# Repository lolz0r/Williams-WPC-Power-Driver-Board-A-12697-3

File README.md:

# Williams WPC power/driver replacement

> **WARNING: These are unverified, experimental boards. Use at your own risk.**
> No variant has been physically validated or qualified for production. Simulation
> results, CAD checks and manufacturing files do not establish safe or reliable
> operation. Errors may damage the board, connected equipment or pinball machine.
> Independently review the design and complete first-article testing before use.

This project develops a modern replacement for the Williams **A-12697-3 WPC
Power/Driver Board**, with **Star Trek: The Next Generation L7** as the documented
compatibility and emulation target. It provides rectified supplies, regulated
5 V and 12 V rails, 28 coil/flasher outputs, an 8×8 lamp matrix and five general
illumination triac channels. The board has no firmware. Compatibility with every
A-12697 installation has not been established.

## Variants and sourcing options

| Location | What it contains | Quantity and status |
| --- | --- | --- |
| [JLC-100](variants/jlcpcb-100/README.md) | Latest separate native KiCad variant, derived from JLC-3 with stocked alternative parts, mixed SMT/through-hole assembly files and connector-orientation guides. | Electronics selected for **100 boards plus spares**, using dated JLCPCB inventory snapshots. Experimental; software checks pass, physical and assembler acceptance gates remain open. |
| [JLC-3](variants/jlcpcb/README.md) | Earlier JLCPCB prototype with TPS552892 buck-boost supplies. Its CAD and exports are independent of JLC-100. | Prototype revision with procurement shortfalls. Its standard upload pair covers SMT; through-hole/manual parts and hardware use separate lists. |
| [DigiKey one-board sourcing proposal](variants/jlcpcb-100/output/digikey-1/README.md) | Alternative procurement BOM and itemized USD pricing based on the JLC-100 design. **This is not another released PCB or CPL.** | **One board, no production spares.** Some parts are proposed substitutes requiring engineering review; F115 remains unresolved and unpriced. |
| [Original cost-reduced project](docs/RELEASE_STATUS.md) at the repository root | Preserved parent CAD, earlier regulator design, simulation work and release-candidate exports. | Earlier engineering candidate with its own unresolved verification gates. Root `output/` does not contain the JLC-100 variant. |

Choose the variant first, then use its matching CAD, Gerbers, BOM and CPL.
Substitutions, packages and placement rotations differ between variants.
JLC-1/JLC-2 archives under `variants/jlcpcb/output/` are historical snapshots.

## JLC-100: Gerbers, BOM and centroids

For the latest JLCPCB variant, start with these files:

| File | Purpose |
| --- | --- |
| [Gerbers and drills ZIP](variants/jlcpcb-100/output/release-candidate/gerbers-and-drills.zip) | Bare-board fabrication layers and plated/non-plated drills. |
| [Combined electronics BOM.csv](variants/jlcpcb-100/output/release-candidate/jlcpcb-assembly/BOM.csv) | JLCPCB upload BOM covering all SMT and through-hole electronics, holders and fuse cartridges. |
| [Matching CPL.csv](variants/jlcpcb-100/output/release-candidate/jlcpcb-assembly/CPL.csv) | Matching component centers and corrected supplier placement rotations. Use with the combined BOM above. |
| [BOM/CPL bundle ZIP](variants/jlcpcb-100/output/wpc-JLC-100-BOM-CPL.zip) | Combined upload pair with assembly reference material. |
| [Complete prototype package ZIP](variants/jlcpcb-100/output/wpc-sttng-JLC-100-prototype.zip) | Native CAD, fabrication and assembly outputs, sourcing and recorded verification evidence. |
| [Complete components BOM](variants/jlcpcb-100/output/release-candidate/bom/all-components.csv) | Human-readable assembly/procurement record, including external hardware and zero-quantity DNP/board features. |
| [100-board electronics purchase BOM](variants/jlcpcb-100/output/release-candidate/bom/jlc-electronics-purchase.csv) | Order quantities and stock evidence, including procurement spares. This is not the upload BOM. |
| [External hardware BOM](variants/jlcpcb-100/output/release-candidate/bom/external-hardware.csv) | Heatsinks, screws, nuts and thermal paste for separate procurement and manual fitting. |
| [Native KiCad PCB](variants/jlcpcb-100/wpc_power_driver_cost.kicad_pcb), [schematic](variants/jlcpcb-100/wpc_power_driver_cost.kicad_sch) and [assembly preview](variants/jlcpcb-100/output/release-candidate/3d/perspective.png) | Source design and nominal assembled geometry. |

The combined upload pair describes **one board**. Select the production quantity
in the assembly order; do not multiply CPL entries or include purchasing spares
as placements. There are **440 electronic pieces per board: 345 SMT, 82 soldered
through-hole pieces and 13 inserted fuse cartridges**, grouped into 69 catalog
parts. J115 is purchased as two six-position headers. Separate fuse holders and
cartridges account for the other expanded references.

Read the [upload and manual-assembly instructions](variants/jlcpcb-100/docs/JLCPCB_UPLOAD.md)
and provide the [PCBA remarks](variants/jlcpcb-100/output/release-candidate/jlcpcb-assembly/PCBA-remark.txt).
The cartridge CPL entries use a documented 0.3 mm selection offset for stacked
parts; their physical centers remain at the holders. Heatsinks, fasteners and
paste are in the complete BOM but require separate sourcing and assembly
agreement. An accepted electronics upload alone does not establish complete
mechanical assembly.

Use the [connector orientation guide](variants/jlcpcb-100/output/release-candidate/jlcpcb-assembly/connector-orientation-guide.pdf)
and [preview review notes](variants/jlcpcb-100/docs/CONNECTOR_PREVIEW_REVIEW.md)
to resolve supplier-library discrepancies. The current CPL includes U1 = 90°,
U2/U3 = 270°, J110 = 180° and J113 = 90°; do not apply those offsets again.
J120/J121/J126 are present as C592598 / TE 1-640445-3 and need explicit part
selection and the documented header preparation. Several connector and rectifier
orientations still require assembler review.

For SMT-only work, use the separate [SMT BOM](variants/jlcpcb-100/output/release-candidate/bom/jlc-smt-bom.csv)
and [SMT CPL](variants/jlcpcb-100/output/release-candidate/assembly/jlc-smt-cpl.csv),
with the [through-hole/manual BOM](variants/jlcpcb-100/output/release-candidate/bom/jlc-through-hole-manual.csv)
for the remaining electronics. Generic engineering position reports are not the
assembly upload pair.

The JLC-100 fabrication specification is **four layers, 1.6 mm nominal FR-4,
2 oz finished outer copper / 1 oz inner copper** (70/35/35/70 µm), ENIG and at
least 20 µm finished plated-hole barrel copper. The outline is
449.152 × 272.910 mm. See [FABRICATION.txt](variants/jlcpcb-100/output/release-candidate/FABRICATION.txt)
and [READINESS.json](variants/jlcpcb-100/output/release-candidate/READINESS.json)
for the exact requirements and outstanding gates.

## DigiKey: one-board BOM and pricing

- [DigiKey BOM.csv](variants/jlcpcb-100/output/digikey-1/DigiKey-BOM.csv): original
  and proposed parts, order numbers, references, required/purchase quantities,
  through-hole parts, hardware and substitution notes.
- [Itemized pricing.csv](variants/jlcpcb-100/output/digikey-1/DigiKey-pricing.csv):
  per-part USD prices, quantity breaks, stock snapshots, product source links,
  extended costs and subtotal/complete-total rows.
- [Totals.csv](variants/jlcpcb-100/output/digikey-1/DigiKey-totals.csv): category
  subtotals, minimum-purchase overhead and missing-cost status.
- [DigiKey package ZIP](variants/jlcpcb-100/output/DigiKey-one-board.zip) and
  [sourcing explanation](variants/jlcpcb-100/output/digikey-1/README.md).

The September 14, 2026 estimate has a **$405.60 USD priced purchase subtotal**,
including minimum hardware purchase quantities. Parts allocated to one board
account for $363.30, including one complete thermal-paste syringe; $42.30 is
minimum-purchase excess. Freight, taxes, tariffs, PCB fabrication and assembly
are additional.

**This is a partial estimate: 78 of 79 required procurement lines are priced.**
F115's 0.75 A ceramic time-delay fuse remains required and unpriced, so the final
complete-BOM total is blank. The 28 priced candidate/accessory lines require
engineering review; the JLC-100 SPICE results do not qualify these substitutions.
No DigiKey-specific PCB, Gerbers or CPL has been released.

## Verification and reproduction

JLC-100 retains 230 passing ngspice engineering cases and recorded CAD,
manufacturing, inventory and assembly-file checks. These use engineering models,
including an averaged supply controller. They do not establish physical thermal,
fault, startup, harness-fit or production performance. Stock snapshots are not
reservations. Supplier part selection and manual operations remain review items.

See the variant's [simulation scope](variants/jlcpcb-100/docs/SPICE_SCOPE.md),
[inventory and assembly notes](variants/jlcpcb-100/docs/INVENTORY_AND_ASSEMBLY.md),
[first-article procedure](variants/jlcpcb-100/docs/FIRST_ARTICLE.md), and
[accepted verification manifest](variants/jlcpcb-100/output/release-candidate/reports/verification-manifest.json).
The later [native connector-tab audit](variants/jlcpcb-100/output/verification/revision/native-connector-tabs.json)
checks 37 single-row connector wall directions in nominal CAD; J113 and physical
cable compatibility retain the documented limitations. That audit and the
DigiKey proposal are additional repository records outside the existing complete
prototype ZIP.

Each variant's routed native PCB is authoritative. Open it with its adjacent
schematics, local symbols, footprints and models. Historical placement generators
and one-time migrations must not overwrite the routed source. Follow the chosen
variant's README and verification instructions when regenerating exports.

The large catalog-search cache is retained as lossless gzip; see the
[research storage notes](variants/jlcpcb-100/research/README.md) to unpack it.

The DigiKey CSVs can be regenerated from their saved pricing facts at the
repository root:

```sh
python3 variants/jlcpcb-100/tools/build_digikey_one_board.py
```

For the preserved parent project, use its [release status](docs/RELEASE_STATUS.md),
[verification instructions](docs/VERIFICATION.md), [Gerbers](output/release-candidate/gerbers-and-drills.zip),
[purchase BOM](output/release-candidate/bom/purchase-bom.csv),
[schematic PDF](output/release-candidate/schematic/schematic.pdf) and
[fabrication specification](output/release-candidate/FABRICATION.txt).
Older root exports directly under `output/` are superseded by the parent's
`output/release-candidate/`. The [historical design narrative](docs/HISTORICAL_DESIGN.md)
records earlier selections and estimates.

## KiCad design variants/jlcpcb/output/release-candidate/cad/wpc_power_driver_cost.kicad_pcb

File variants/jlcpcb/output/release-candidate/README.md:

# JLC-3 controlled prototype

Upload the matching `gerbers-and-drills.zip`, `bom/jlc-smt-bom.csv` and
`assembly/jlc-smt-cpl.csv` to JLCPCB. See `READINESS.json` and
`docs/PROTOTYPE_JLC3.md` for build scope, settings and first-article checks.
Through-hole/manual parts and hardware are listed separately in `bom/`.
Editable KiCad 10 sources, libraries and models are in `cad/`.
This package supports building a test prototype; physical qualification remains to be performed.

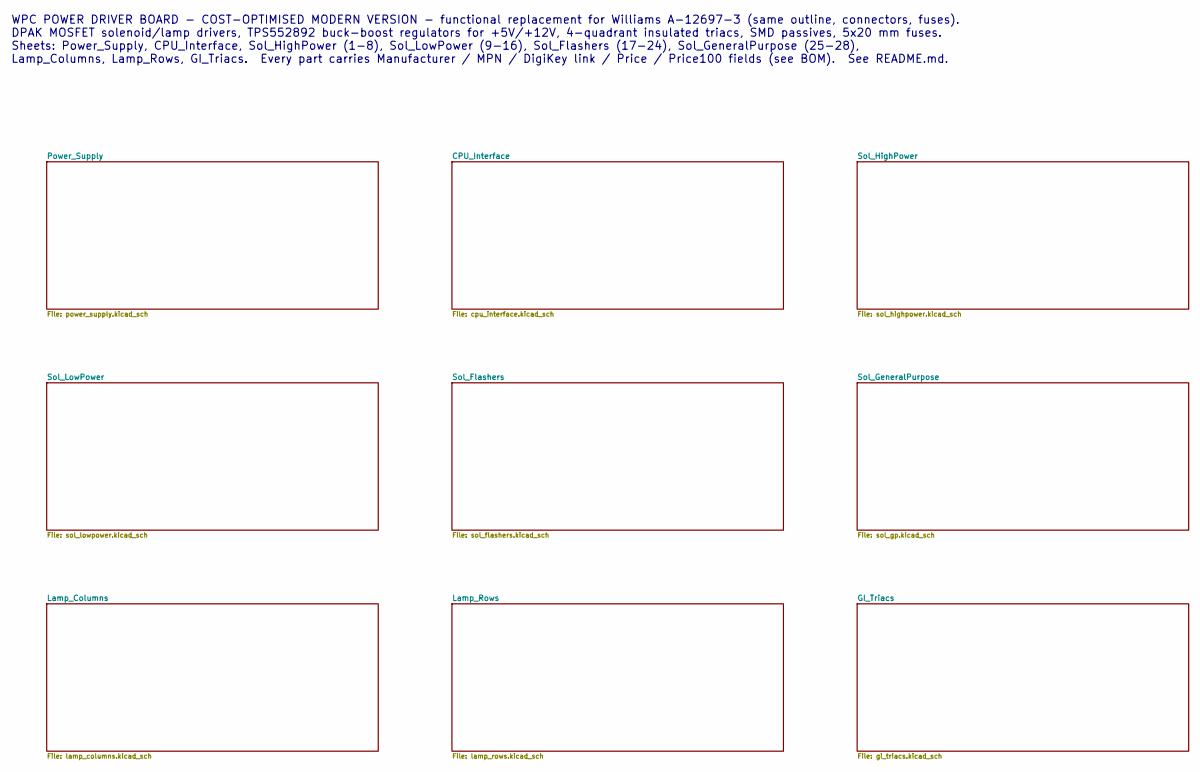
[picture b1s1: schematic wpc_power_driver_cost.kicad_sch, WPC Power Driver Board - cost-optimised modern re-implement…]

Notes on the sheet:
WPC POWER DRIVER BOARD - COST-OPTIMISED MODERN VERSION - functional replacement for Williams A-12697-3 (same outline, connectors, fuses). DPAK MOSFET solenoid/lamp drivers, TPS552892 buck-boost regulators for +5V/+12V, 4-quadrant insulated triacs, SMD passives, 5x20 mm fuses. Sheets: Power_Supply, 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

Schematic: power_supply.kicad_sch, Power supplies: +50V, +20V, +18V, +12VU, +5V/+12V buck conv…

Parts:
BR3: GBPC3510; Diode_Bridge_28.6x28.6x7.3mm_P18.0mm_P11.6mm; MPN GBPC3510W-E4/51; JLCPCB Part C435891
C2, C4, C9, C12: 330uF; CP_Radial_D8.0mm_P5.00mm; MPN EEU-FR1E331B; JLCPCB Part C1579638
C5, C6, C7, C11, C30: 10000uF 35V; CP_Radial_D26.0mm_P10.00mm_SnapIn; MPN B41252A7109M000; JLCPCB Part C6130373
C8, C32: 2200uF 100V; CP_Radial_D25.0mm_P10.00mm_SnapIn; MPN LLS2A222MELA; JLCPCB Part C1582025
C33, C34, C38, C39, C40, C44, C46, C49, C50, C51, C53, C56, C57, C58: 10uF; C_1210_3225Metric; MPN CL32B106KBJNNWE; JLCPCB Part C3844168
C35, C41, C45, C47, C48, C52, C54, C55: 100nF; C_0402_1005Metric; MPN GRM155R71H104KE14D; JLCPCB Part C77020
C36: 100nF; C_0805_2012Metric; MPN CC0805KRX7R9BB104; JLCPCB Part C49678
C37: 680pF; C_0805_2012Metric; MPN CC0805JRNPO9BN681; JLCPCB Part C107121
C42: 330nF; C_0805_2012Metric; MPN CL21B334KBFNNNE; JLCPCB Part C73142
C43: 1nF; C_0805_2012Metric; MPN CC0805JRNPO9BN102; JLCPCB Part C62774
D101, D102, D103, D104: STPS20M100ST; TO220_Schottky_AKA_5772; MPN STPS20M100ST; JLCPCB Part C222114
D105, D106, D107, D108, D109, D110, D111, D112, D113, D114, D115, D116: STPS20M100S; D2PAK_Schottky_AKA; MPN STPS20M100SG-TR; JLCPCB Part C969989
F103, F104, F105, F116: 3A S.B.; Fuseholder_Clip-5x20mm_Keystone_3517_Inline_P23.11x6.76mm_D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; MPN 0239003.MXP; JLCPCB Part C142824
F111, F113: 5A S.B.; Fuseholder_Clip-5x20mm_Keystone_3517_Inline_P23.11x6.76mm_D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; MPN 0239005.MXP; JLCPCB Part C151086
F112: 7A S.B.; Fuseholder_Clip-5x20mm_Keystone_3517_Inline_P23.11x6.76mm_D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; MPN 0239007.MXP; JLCPCB Part C3161084
F114: 8A; Fuseholder_Clip-5x20mm_Keystone_3517_Inline_P23.11x6.76mm_D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; MPN 0217008.MXP; JLCPCB Part C2936126
F115: 3/4A S.B.; Fuseholder_Clip-5x20mm_Keystone_3517_Inline_P23.11x6.76mm_D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; MPN 0239.750MXP; JLCPCB Part C3157012
H1, H2, H3, H4, H5, H6, H7, H8: M4; MountingHole_4.3mm_M4
J101: J101 xformer 9VAC (Red) / 13VAC (Blu-Wht); Molex_KK-396_A-41791-0007_1x07_P3.96mm_Vertical; MPN 26604070; JLCPCB Part C587091
J102: J102 xformer 16VAC (Wht-Red) / solenoid ~51VAC (B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; Molex_KK-396_A-41791-0009_1x09_P3.96mm_Vertical; MPN 0026604090; JLCPCB Part C17420444
J103: J103 ground to 8-driver board (all four pins grou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; Molex_KK-396_A-41791-0004_1x04_P3.96mm_Vertical; MPN 26604040; JLCPCB Part C240824
J104: J104 fused 51VAC (F112, pins 1/2) to Fliptronic I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; Molex_KK-396_A-41791-0005_1x05_P3.96mm_Vertical; MPN 26604050; JLCPCB Part C505166
J106: J106 +20V to backbox flashlamps (pins 1-4 open, k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; Molex_KK-396_A-41791-0005_1x05_P3.96mm_Vertical; MPN 26604050; JLCPCB Part C505166
J107: J107 +50V (F103/F104/F105) and +20V (pins 5,6) to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; Molex_KK-396_A-41791-0006_1x06_P3.96mm_Vertical; MPN 0026604060; JLCPCB Part C17656945
J108: J108 +50V (F103/F104/F105) to cabinet (N/C on STT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; Molex_KK-396_A-41791-0003_1x03_P3.96mm_Vertical; MPN 26604030; JLCPCB Part C240823
J109: J109 spare (N/C); Molex_KK-396_A-41791-0007_1x07_P3.96mm_Vertical; MPN 26604070; JLCPCB Part C587091
J110: J110 spare (N/C); Molex_KK-396_A-41791-0009_1x09_P3.96mm_Vertical; MPN 0026604090; JLCPCB Part C17420444
J112: J112 xformer 9.8VAC (Wht-Grn); Molex_KK-396_A-41791-0005_1x05_P3.96mm_Vertical; MPN 26604050; JLCPCB Part C505166
J114: J114 +12V/+5V/GND to CPU J210, Fliptronic J904, 8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; Molex_KK-396_A-41791-0007_1x07_P3.96mm_Vertical; MPN 26604070; JLCPCB Part C587091
J116: J116 +12V power (unregulated) / GND / +5V to coin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; Molex_KK-396_A-41791-0004_1x04_P3.96mm_Vertical; MPN 26604040; JLCPCB Part C240824
J117: J117 +12V power (unregulated) / GND / +5V to DMD 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; Molex_KK-396_A-41791-0004_1x04_P3.96mm_Vertical; MPN 26604040; JLCPCB Part C240824
J118: J118 +12V power (unregulated) / GND / +5V to play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; Molex_KK-396_A-41791-0004_1x04_P3.96mm_Vertical; MPN 26604040; JLCPCB Part C240824
L1, L2: 10uH; L_Bourns_SRP1245A; MPN SRP1265A-100M; JLCPCB Part C840531
LED1, LED2, LED4, LED5, LED6, LED7: LED red; LED_0805_2012Metric; MPN NCD0805R1; JLCPCB Part C84256
R192: 470; R_0805_2012Metric; MPN 0805W8F4700T5E; JLCPCB Part C17710
R193: 1K; R_0805_2012Metric; MPN 0805W8F1001T5E; JLCPCB Part C17513
R194, R196, R250, R251: 1.5K; R_0805_2012Metric; MPN 0805W8F1501T5E; JLCPCB Part C4310
R259, R260: 15K; R_2512_6332Metric; MPN RC2512JK-0715KL; JLCPCB Part C1882622
R261: 118K; R_0805_2012Metric; MPN RC0805FR-07118KL; JLCPCB Part C274001
R262: 29.4K; R_0805_2012Metric; MPN RC0805FR-0729K4L; JLCPCB Part C273956
R263, R269: 49.9K; R_0805_2012Metric; MPN 0805W8F4992T5E; JLCPCB Part C17719
R264: 6.65K; R_0805_2012Metric; MPN RT0805BRD076K65L; JLCPCB Part C865625
R265: 2.1K; R_0805_2012Metric; MPN RT0805BRD072K1L; JLCPCB Part C865367
R266: 33.2K; R_0805_2012Metric; MPN 0805W8F3322T5E; JLCPCB Part C37252
R267: 130K; R_0805_2012Metric; MPN RC0805FR-07130KL; JLCPCB Part C483008
R268: 20K; R_0805_2012Metric; MPN 0805W8F2002T5E; JLCPCB Part C4328
R270: 18K; R_0805_2012Metric; MPN RT0805BRD0718KL; JLCPCB Part C706223
R271: 2K; R_0805_2012Metric; MPN RT0805BRD072KL; JLCPCB Part C865384
R272: 42.2K; R_0805_2012Metric; MPN 0805W8F4222T5E; JLCPCB Part C17686
R326: 13m; R_2512_6332Metric; MPN RL2512FK-070R013L; JLCPCB Part C705606
R327: 33m; R_2512_6332Metric; MPN RL2512FK-070R033L; JLCPCB Part C705608
TP1: TP1 +12VU; TestPoint_THTPad_D2.0mm_Drill1.0mm
TP2: TP2 +5V; TestPoint_THTPad_D2.0mm_Drill1.0mm
TP3: TP3 +12V; TestPoint_THTPad_D2.0mm_Drill1.0mm
TP5: TP5 GND; TestPoint_THTPad_D2.0mm_Drill1.0mm
TP6: TP6 +50V; TestPoint_THTPad_D2.0mm_Drill1.0mm
TP7: TP7 +20V; TestPoint_THTPad_D2.0mm_Drill1.0mm
TP8: TP8 +18V; TestPoint_THTPad_D2.0mm_Drill1.0mm
TP9: TP9 +5V_RAW; TestPoint_THTPad_D2.0mm_Drill1.0mm
U20, U21: TPS552892RYQR; TI_RYQ0021B_5x3mm; MPN TPS552892RYQR; JLCPCB Part C19272254

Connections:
+5V: C4.1, C9.1, J114.3, J114.4, J116.4, J117.4, J118.4, R192.1, R264.1, R326.2, TP2.1, U20.13 (ISN); also elsewhere on the board
+12V: C2.1, C12.1, F115.1, R193.1, R270.1, R327.2, TP3.1, U21.13 (ISN); also elsewhere on the board
+12VU: C30.1, D113.1 (K), D114.1 (K), J116.2, J117.2, J118.2, R250.1, TP1.1
+12V_F: F115.2, J114.1, J114.2, R251.1
+18V: C6.1, C7.1, C39.1, C40.1, C54.1, C56.1, C57.1, D101.1 (K), D102.1 (K), R196.1, R267.1, TP8.1, U21.7 (VIN); also elsewhere on the board
+20V: C11.1, D109.1 (K), D110.1 (K), J106.5, J107.5, J107.6, R194.1, TP7.1; also elsewhere on the board
+50V: BR3.1 (+), C8.1, C32.1, F103.1, F104.1, F105.1, R259.1, R260.1, TP6.1; also elsewhere on the board
+50V_F103: F103.2, J107.1, J108.1
+50V_F104: F104.2, J107.2, J108.2
+50V_F105: F105.2, J107.3, J108.3
/Power_Supply/+5V_RAW: C5.1, C33.1, C34.1, C47.1, C49.1, C50.1, D105.1 (K), D106.1 (K), R261.1, TP9.1, U20.7 (VIN)
/Power_Supply/AC13_A_F: D101.2 (A), D103.1 (K), F114.2
/Power_Supply/AC98_A_F: D113.2 (A), D115.1 (K), F116.2
/Power_Supply/U20_BOOT1: C35.1, U20.20 (BOOT1)
/Power_Supply/U20_BOOT2: C45.1, U20.19 (BOOT2)
/Power_Supply/U20_CC: C36.1, R266.2
/Power_Supply/U20_COMP: C37.1, R266.1, U20.15 (COMP)
/Power_Supply/U20_EN: R261.2, R262.1, U20.1 (EN)
/Power_Supply/U20_FB: R264.2, R265.1, U20.14 (FB)
/Power_Supply/U20_REG: C38.1, C48.1, C51.1, R326.1, U20.11 (VOUT), U20.12 (ISP)
/Power_Supply/U20_RT: R263.1, U20.6 (FSW)
/Power_Supply/U20_SW1: C35.2, L1.1, U20.8 (SW1)
/Power_Supply/U20_SW2: C45.2, L1.2, U20.10 (SW2)
/Power_Supply/U20_VCC: C46.1, U20.18 (VCC)
/Power_Supply/U21_BOOT1: C41.1, U21.20 (BOOT1)
/Power_Supply/U21_BOOT2: C52.1, U21.19 (BOOT2)
/Power_Supply/U21_CC: C42.1, R272.2
/Power_Supply/U21_COMP: C43.1, R272.1, U21.15 (COMP)
/Power_Supply/U21_EN: R267.2, R268.1, U21.1 (EN)
/Power_Supply/U21_FB: R270.2, R271.1, U21.14 (FB)
/Power_Supply/U21_REG: C44.1, C55.1, C58.1, R327.1, U21.11 (VOUT), U21.12 (ISP)
/Power_Supply/U21_RT: R269.1, U21.6 (FSW)
/Power_Supply/U21_SW1: C41.2, L2.1, U21.8 (SW1)
/Power_Supply/U21_SW2: C52.2, L2.2, U21.10 (SW2)
/Power_Supply/U21_VCC: C53.1, U21.18 (VCC)
AC9_A: F113.1, J101.1
AC9_AF: D105.2 (A), D107.1 (K), F113.2; also elsewhere on the board
AC9_B: D106.2 (A), D108.1 (K), J101.2; also elsewhere on the board
AC13_A: F114.1, J101.4, J101.5
AC13_B: D102.2 (A), D104.1 (K), J101.6, J101.7
AC16_A: F111.1, J102.1, J102.2
AC16_A_F: D109.2 (A), D111.1 (K), F111.2, J104.4; also elsewhere on the board
AC16_B: D110.2 (A), D112.1 (K), J102.3, J102.4, J104.5; also elsewhere on the board
AC98_A: F116.1, J112.1, J112.2
AC98_B: D114.2 (A), D116.1 (K), J112.3, J112.5
ACSOL_A: F112.1, J102.5, J102.6; also elsewhere on the board
ACSOL_A_F: BR3.3, F112.2, J104.1; also elsewhere on the board
ACSOL_B: BR3.4, J102.8, J102.9, J104.2; also elsewhere on the board

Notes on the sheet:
+50V solenoid supply (51 VAC winding -> ~70 V DC, 78 V peak unloaded)
BR4: discrete Schottky bridge D109-D112 (D2PAK tabs = cathodes: D109/D110 on the +20V pour, D111/D112 on the AC pours)
+20V flashlamp supply
BR1: D101-D104 STPS20M100ST TO-220, each with 577202B00000G heatsink (tabs/heatsinks = cathodes; do not join heatsinks)
+18V lamp matrix supply (13.3 VAC); also feeds the +12V digital buck-boost U21
BR2: discrete Schottky bridge D105-D108 (D2PAK tabs = cathodes: D105/D106 on the +5V_RAW pour, D107/D108 on the AC pours)
+5V raw supply (9VAC)
BR5: discrete Schottky bridge D113-D116 (D2PAK tabs = cathodes: D113/D114 on the +12VU pour, D115/D116 on the AC pours)
+12V POWER (unregulated, 9.8VAC): motors, optos, coin door, DMD - J116/J117/J118
Power supplies (windings per manual/pinwiki: 9 VAC red -> +5V, 13.3 VAC blu-wht -> +18V, 16 VAC wht-red -> +20V, 51 VAC blk-yel -> "+50V" (~70 V DC), 9.8 VAC wht-grn -> +12V power). Each secondary is fused (F111-F114, F116, 5x20 mm) before its bridge: GBPC3510W block (BR3, 6223BG basket heatsink); 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
U20: TPS552892 buck-boost / 395 kHz / PFM / +5V / current limit 3.85 A nominal
Local output ceramics precede the sense resistor; bulk capacitors and feedback follow it. EXTVCC open selects internal VCC.
U21: TPS552892 buck-boost / 395 kHz / PFM / +12V / current limit 1.52 A nominal

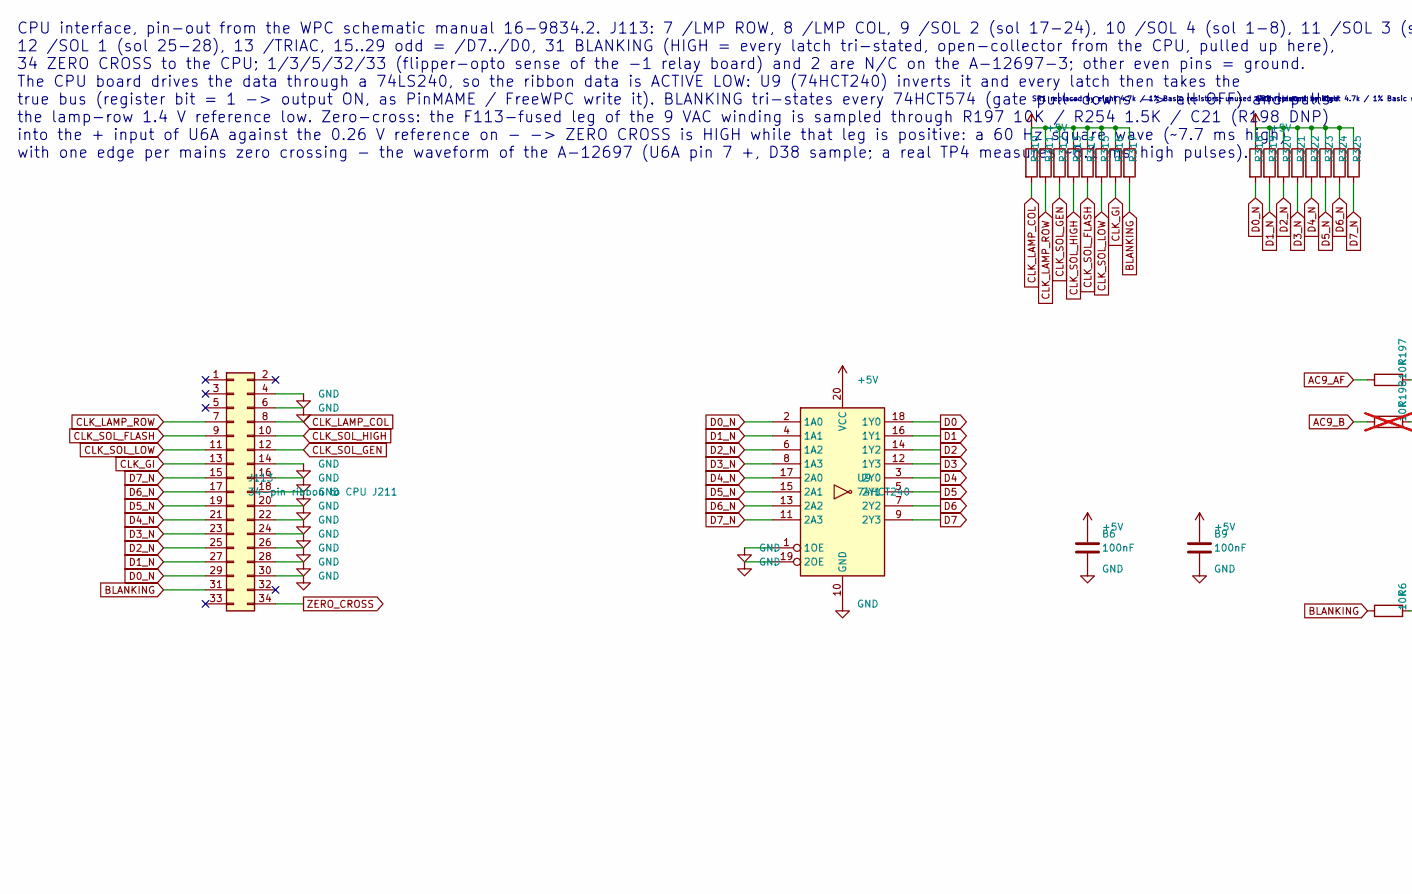
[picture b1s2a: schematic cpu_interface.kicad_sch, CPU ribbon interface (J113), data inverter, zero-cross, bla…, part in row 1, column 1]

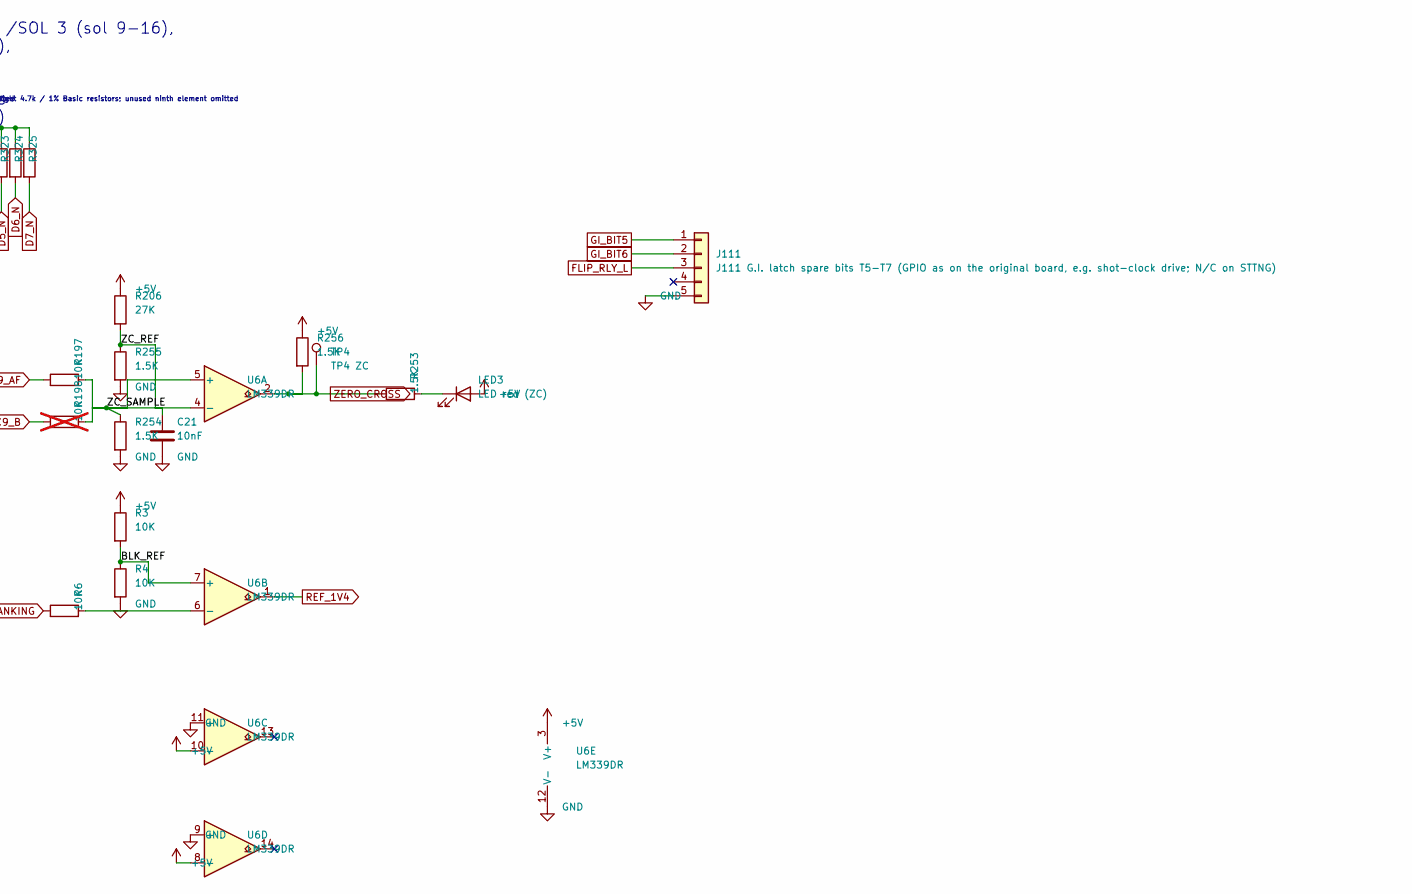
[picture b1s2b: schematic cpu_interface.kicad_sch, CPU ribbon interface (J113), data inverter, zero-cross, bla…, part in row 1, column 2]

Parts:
B6, B9: 100nF; C_0805_2012Metric; MPN CC0805KRX7R9BB104; JLCPCB Part C49678
C21: 10nF; C_0805_2012Metric; MPN CL21B103KBANNNC; JLCPCB Part C1710
J111: J111 G.I. latch spare bits T5-T7 (GPIO as on the 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; Molex_KK-254_AE-6410-05A_1x05_P2.54mm_Vertical; MPN 22232051; JLCPCB Part C588986
J113: 34-pin ribbon to CPU J211; 3M_N2534_6002_RB; MPN N2534-6002-RB; JLCPCB Part C17502444
LED3: LED red (ZC); LED_0805_2012Metric; MPN NCD0805R1; JLCPCB Part C84256
R3, R4, R6, R197: 10K; R_0805_2012Metric; MPN 0805W8F1002T5E; JLCPCB Part C17414
R198: 10K; R_0805_2012Metric; MPN RC0805FR-0710KL; not fitted
R206: 27K; R_0805_2012Metric; MPN 0805W8F2702T5E; JLCPCB Part C17593
R253, R254, R255, R256: 1.5K; R_0805_2012Metric; MPN 0805W8F1501T5E; JLCPCB Part C4310
R310, R311, R312, R313, R314, R315, R316, R317, R318, R319, R320, R321, R322, R323, R324, R325: 4.7K; R_0805_2012Metric; MPN 0805W8F4701T5E; JLCPCB Part C17673
TP4: TP4 ZC; TestPoint_THTPad_D2.0mm_Drill1.0mm
U6: LM339DR; SOIC-14_3.9x8.7mm_P1.27mm; MPN LM339DR; JLCPCB Part C7948
U9: 74HCT240; SOIC-20W_7.5x12.8mm_P1.27mm; MPN SN74HCT240DWR; JLCPCB Part C132264

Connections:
+5V: B6.1, B9.1, LED3.2 (A), R3.1, R206.1, R256.1, R310.1, R311.1, R312.1, R313.1, R314.1, R315.1, R316.1, R317.1, R318.1, R319.1, R320.1, R321.1, R322.1, R323.1, R324.1, R325.1, U6.3 (V+), U6.8 (-), U6.10 (-), U9.20 (VCC); also elsewhere on the board
/CPU_Interface/BLK_REF: R3.2, R4.1, U6.7 (+)
/CPU_Interface/ZC_REF: R206.2, R255.1, U6.4 (-)
/CPU_Interface/ZC_SAMPLE: C21.1, R197.2, R198.2, R254.1, U6.5 (+)
AC9_AF: R197.1; also elsewhere on the board
AC9_B: R198.1; also elsewhere on the board
BLANKING: J113.31, R6.1, R317.2; also elsewhere on the board
CLK_GI: J113.13, R316.2; also elsewhere on the board
CLK_LAMP_COL: J113.8, R310.2; also elsewhere on the board
CLK_LAMP_ROW: J113.7, R311.2; also elsewhere on the board
CLK_SOL_FLASH: J113.9, R314.2; also elsewhere on the board
CLK_SOL_GEN: J113.12, R312.2; also elsewhere on the board
CLK_SOL_HIGH: J113.10, R313.2; also elsewhere on the board
CLK_SOL_LOW: J113.11, R315.2; also elsewhere on the board
D0: U9.18 (1Y0); also elsewhere on the board
D0_N: J113.29, R318.2, U9.2 (1A0)
D1: U9.16 (1Y1); also elsewhere on the board
D1_N: J113.27, R319.2, U9.4 (1A1)
D2: U9.14 (1Y2); also elsewhere on the board
D2_N: J113.25, R320.2, U9.6 (1A2)
D3: U9.12 (1Y3); also elsewhere on the board
D3_N: J113.23, R321.2, U9.8 (1A3)
D4: U9.3 (2Y0); also elsewhere on the board
D4_N: J113.21, R322.2, U9.17 (2A0)
D5: U9.5 (2Y1); also elsewhere on the board
D5_N: J113.19, R323.2, U9.15 (2A1)
D6: U9.7 (2Y2); also elsewhere on the board
D6_N: J113.17, R324.2, U9.13 (2A2)
D7: U9.9 (2Y3); also elsewhere on the board
D7_N: J113.15, R325.2, U9.11 (2A3)
FLIP_RLY_L: J111.3; also elsewhere on the board
GI_BIT5: J111.1; also elsewhere on the board
GI_BIT6: J111.2; also elsewhere on the board
unnamed: LED3.1 (K), R253.2
unnamed: R6.2, U6.6 (-)
REF_1V4: U6.1; also elsewhere on the board
ZERO_CROSS: J113.34, R253.1, R256.2, TP4.1, U6.2

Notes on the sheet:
CPU interface, pin-out from the WPC schematic manual 16-9834.2. J113: 7 /LMP ROW, 8 /LMP COL, 9 /SOL 2 (sol 17-24), 10 /SOL 4 (sol 1-8), 11 /SOL 3 (sol 9-16), 12 /SOL 1 (sol 25-28), 13 /TRIAC, 15..29 odd = /D7../D0, 31 BLANKING (HIGH = every latch tri-stated, open-collector from the CPU, pulled up 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
SR1 replaced by eight 4.7k / 1% Basic resistors; unused ninth element omitted
SR2 replaced by eight 4.7k / 1% Basic resistors; unused ninth element omitted

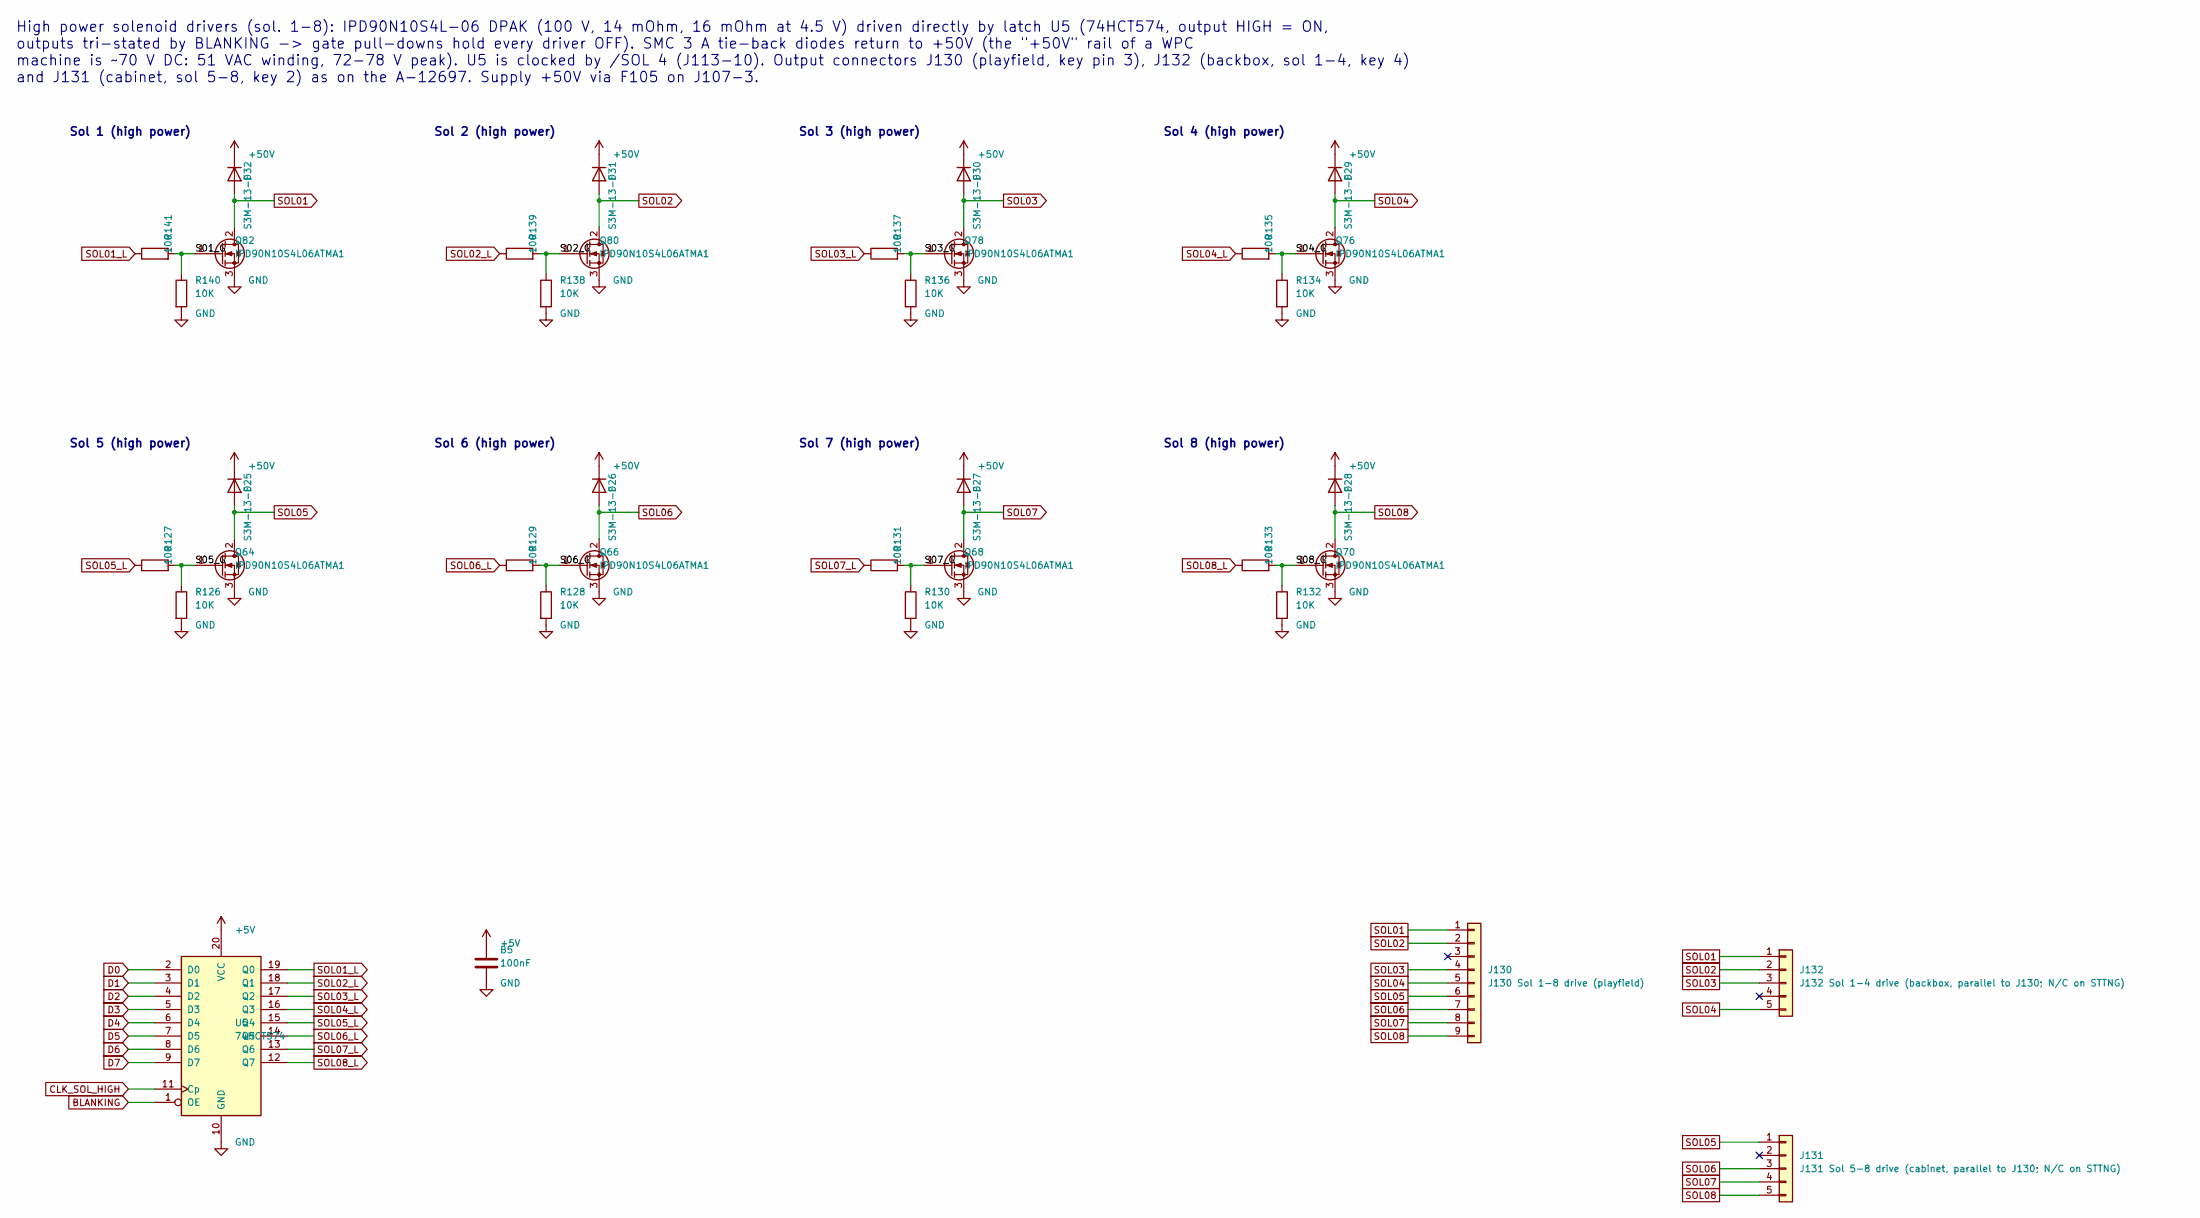
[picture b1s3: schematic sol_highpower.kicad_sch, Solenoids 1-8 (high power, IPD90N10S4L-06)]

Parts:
B5: 100nF; C_0805_2012Metric; MPN CC0805KRX7R9BB104; JLCPCB Part C49678
D25, D26, D27, D28, D29, D30, D31, D32: S3M-13-F; D_SMC; MPN S3M-13-F; JLCPCB Part C460944
J130: J130 Sol 1-8 drive (playfield); Molex_KK-396_A-41791-0009_1x09_P3.96mm_Vertical; MPN 0026604090; JLCPCB Part C17420444
J131: J131 Sol 5-8 drive (cabinet, parallel to J130; N/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; Molex_KK-396_A-41791-0005_1x05_P3.96mm_Vertical; MPN 26604050; JLCPCB Part C505166
J132: J132 Sol 1-4 drive (backbox, parallel to J130; N/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; Molex_KK-396_A-41791-0005_1x05_P3.96mm_Vertical; MPN 26604050; JLCPCB Part C505166
Q64, Q66, Q68, Q70, Q76, Q78, Q80, Q82: IPD90N10S4L06ATMA1; TO-252-2; MPN IPD90N10S4L06ATMA1; JLCPCB Part C5440942
R126, R128, R130, R132, R134, R136, R138, R140: 10K; R_0805_2012Metric; MPN 0805W8F1002T5E; JLCPCB Part C17414
R127, R129, R131, R133, R135, R137, R139, R141: 100; R_0805_2012Metric; MPN 0805W8F1000T5E; JLCPCB Part C17408
U5: 74HCT574; SOIC-20W_7.5x12.8mm_P1.27mm; MPN SN74HCT574DWR; JLCPCB Part C6788

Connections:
+5V: B5.1, U5.20 (VCC); also elsewhere on the board
+50V: D25.1 (K), D26.1 (K), D27.1 (K), D28.1 (K), D29.1 (K), D30.1 (K), D31.1 (K), D32.1 (K); also elsewhere on the board
/Sol_HighPower/S01_G: Q82.1 (G), R140.1, R141.2
/Sol_HighPower/S02_G: Q80.1 (G), R138.1, R139.2
/Sol_HighPower/S03_G: Q78.1 (G), R136.1, R137.2
/Sol_HighPower/S04_G: Q76.1 (G), R134.1, R135.2
/Sol_HighPower/S05_G: Q64.1 (G), R126.1, R127.2
/Sol_HighPower/S06_G: Q66.1 (G), R128.1, R129.2
/Sol_HighPower/S07_G: Q68.1 (G), R130.1, R131.2
/Sol_HighPower/S08_G: Q70.1 (G), R132.1, R133.2
BLANKING: U5.1 (OE); also elsewhere on the board
CLK_SOL_HIGH: U5.11 (Cp); also elsewhere on the board
D0: U5.2 (D0); also elsewhere on the board
D1: U5.3 (D1); also elsewhere on the board
D2: U5.4 (D2); also elsewhere on the board
D3: U5.5 (D3); also elsewhere on the board
D4: U5.6 (D4); also elsewhere on the board
D5: U5.7 (D5); also elsewhere on the board
D6: U5.8 (D6); also elsewhere on the board
D7: U5.9 (D7); also elsewhere on the board
SOL01: D32.2 (A), J130.1, J132.1, Q82.2 (D)
SOL01_L: R141.1, U5.19 (Q0)
SOL02: D31.2 (A), J130.2, J132.2, Q80.2 (D)
SOL02_L: R139.1, U5.18 (Q1)
SOL03: D30.2 (A), J130.4, J132.3, Q78.2 (D)
SOL03_L: R137.1, U5.17 (Q2)
SOL04: D29.2 (A), J130.5, J132.5, Q76.2 (D)
SOL04_L: R135.1, U5.16 (Q3)
SOL05: D25.2 (A), J130.6, J131.1, Q64.2 (D)
SOL05_L: R127.1, U5.15 (Q4)
SOL06: D26.2 (A), J130.7, J131.3, Q66.2 (D)
SOL06_L: R129.1, U5.14 (Q5)
SOL07: D27.2 (A), J130.8, J131.4, Q68.2 (D)
SOL07_L: R131.1, U5.13 (Q6)
SOL08: D28.2 (A), J130.9, J131.5, Q70.2 (D)
SOL08_L: R133.1, U5.12 (Q7)

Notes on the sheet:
Sol 1 (high power)
Sol 2 (high power)
Sol 3 (high power)
Sol 4 (high power)
Sol 5 (high power)
Sol 6 (high power)
Sol 7 (high power)
Sol 8 (high power)
High power solenoid drivers (sol. 1-8): IPD90N10S4L-06 DPAK (100 V, 14 mOhm, 16 mOhm at 4.5 V) driven directly by latch U5 (74HCT574, output HIGH = ON, outputs tri-stated by BLANKING -> gate pull-downs hold every driver OFF). SMC 3 A tie-back diodes return to +50V (the "+50V" rail of a WPC machine 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
